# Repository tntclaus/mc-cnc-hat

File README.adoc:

= Makers' Comrade CNC HAT

Модели шилдов, которые превращают Raspberry в много-осевой ЧПУ с высокой производительностью.

Поддерживаются Raspberry Pi 3B, 3B+, 4 и другие микрокомпьютеры семейства Pi, с колодкой имеющей 40 gpio  (например, Orange Pi 3B).

== Модели

// === 5-осевой шилд
//
// //TODO:
//
// С независимыми UART линиями, в первую очередь для TMC2208, TMC2209 или для DRV8820, A4988 — обычный режим с конфигурацией через перемычки MS1,MS2,MS3 и других драйвера, поддерживающие DIR/STEP.
//
// xref:kicad/mc_cnc_hat_x5/README.adoc[]
//

=== 7-осевой шилд с CAN bus

image::docs/photo_mc_cnc_hat_x7_canbus.jpeg[]

Шилд для управления 7 двигателями ЧПУ и CAN bus периферией для Raspberry Pi 3B/3B+/4B и Orange Pi 3B (не проверялось, но должно работать).

xref:kicad/mc_cnc_hat_x7_canbus/README.adoc[]

=== 8-осевой шилд

image::docs/photo_mc_cnc_hat_x8.png[]

С двумя общими UART линиями для драйверов TMC2209 или для DRV8820, A4988 — обычный режим с конфигурацией через перемычки MS1,MS2,MS3 и других драйвера, поддерживающие DIR/STEP.

xref:kicad/mc_cnc_hat_x7_canbus/README.adoc[]

== Общие для всех моделей возможности

* Одновременное управление 5-7 драйверами шаговых двигателей:
** Поддерживаемые драйвера:
*** TMC2209, TMC2208 — режим UART с указанием адреса через перемычки MS1/MS2;
*** DRV8820, A4988 — обычный режим с конфигурацией через перемычки MS1,MS2,MS3;
*** Любые другие драйвера, поддерживающие DIR/STEP.
* Суммарная пиковая производительность всех двигателей 1018 тыс. шагов/секунду (Klipper с патчем, Linux CNC не тестировался, но вероятно будет результат того же порядка).
* Поддержка концевиков для осей X, Y, Z, A, B, C как стандартного типа, так и DIAG выходов для безсенсорной парковки драйвера TMC2209.
* Поддержка дополнительного концевика (например, для датчика наличия/движения филамента 3д принтера).
* Поддерживаемые системы: Linux CNC (не тестировалось), Klipper.

== Инструкция по установке

Инструкция тут: xref:docs/klipper.adoc[]

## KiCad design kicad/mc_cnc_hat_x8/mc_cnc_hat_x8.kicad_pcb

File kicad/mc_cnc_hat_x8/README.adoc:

= Makers' Comrade CNC Hat (x8 drivers)

image::../../docs/photo_mc_cnc_hat_x8.png[]

Шилд для управления 8 двигателями ЧПУ для Raspberry Pi 3B/3B+/4B и Orange Pi 3B (не проверялось, но должно работать).

С двумя общими UART линиями для драйверов TMC2209 или для DRV8820, A4988 — обычный режим с конфигурацией через перемычки MS1,MS2,MS3 и других драйвера, поддерживающие DIR/STEP.

TMC2208 можно установить по 1 на каждую UART линию, при условии что на остальных местах будут драйвера не требующие использования UART (например, DRV8820).

Первая UART линия общая для X, X1, Y, Z.
Вторая UART линия общая для A, A1, B, C.

== Возможности

* Одновременное управление 8 драйверами шаговых двигателей. Поддерживаемые драйвера:
** TMC2209 — режим UART с указанием адреса через перемычки MS1/MS2;
** TMC2208, DRV8820, A4988 — обычный режим с конфигурацией через перемычки MS1,MS2,MS3;
** Любые другие драйвера, поддерживающие DIR/STEP.
* Суммарная пиковая производительность всех двигателей 1018 тыс. шагов/секунду на RPi 3B+ (Klipper из форка https://github.com/tntclaus/klipper[tntclaus/klipper], Linux CNC не тестировался, но вероятно будет результат того же порядка).
* Поддержка концевиков для всех двигателей — как стандартного типа, так и DIAG выходов для безсенсорной парковки драйвера TMC2209.
* Поддерживаемые системы: Linux CNC (не тестировалось), Klipper.

== Использование

Для использования с Klipper см. инструкцию xref:../../docs/klipper.adoc[по настройке Klipper]

Конфигурирование драйверов описано в  xref:../../docs/drivers_x7_x8.adoc[инструкции].

== Пины

.Моторы
|===
|Назначение |Motor X |Motor X1 |Motor Y |Motor Z |Motor A |Motor A1 |Motor B |Motor C

|STEP
|GPIO3
|GPIO6
|GPIO27
|GPIO19
|GPIO23
|GPIO9
|GPIO1
|GPIO20

|DIR
|GPIO2
|GPIO15
|GPIO17
|GPIO13
|GPIO24
|GPIO10
|GPIO12
|GPIO21

|UART
|GPIO5
|GPIO5
|GPIO5
|GPIO5
|GPIO25
|GPIO25
|GPIO25
|GPIO25

|DIAG/Endstop
|GPIO4
|GPIO11
|GPIO0
|GPIO26
|GPIO18
|GPIO8
|GPIO7
|GPIO16
|===

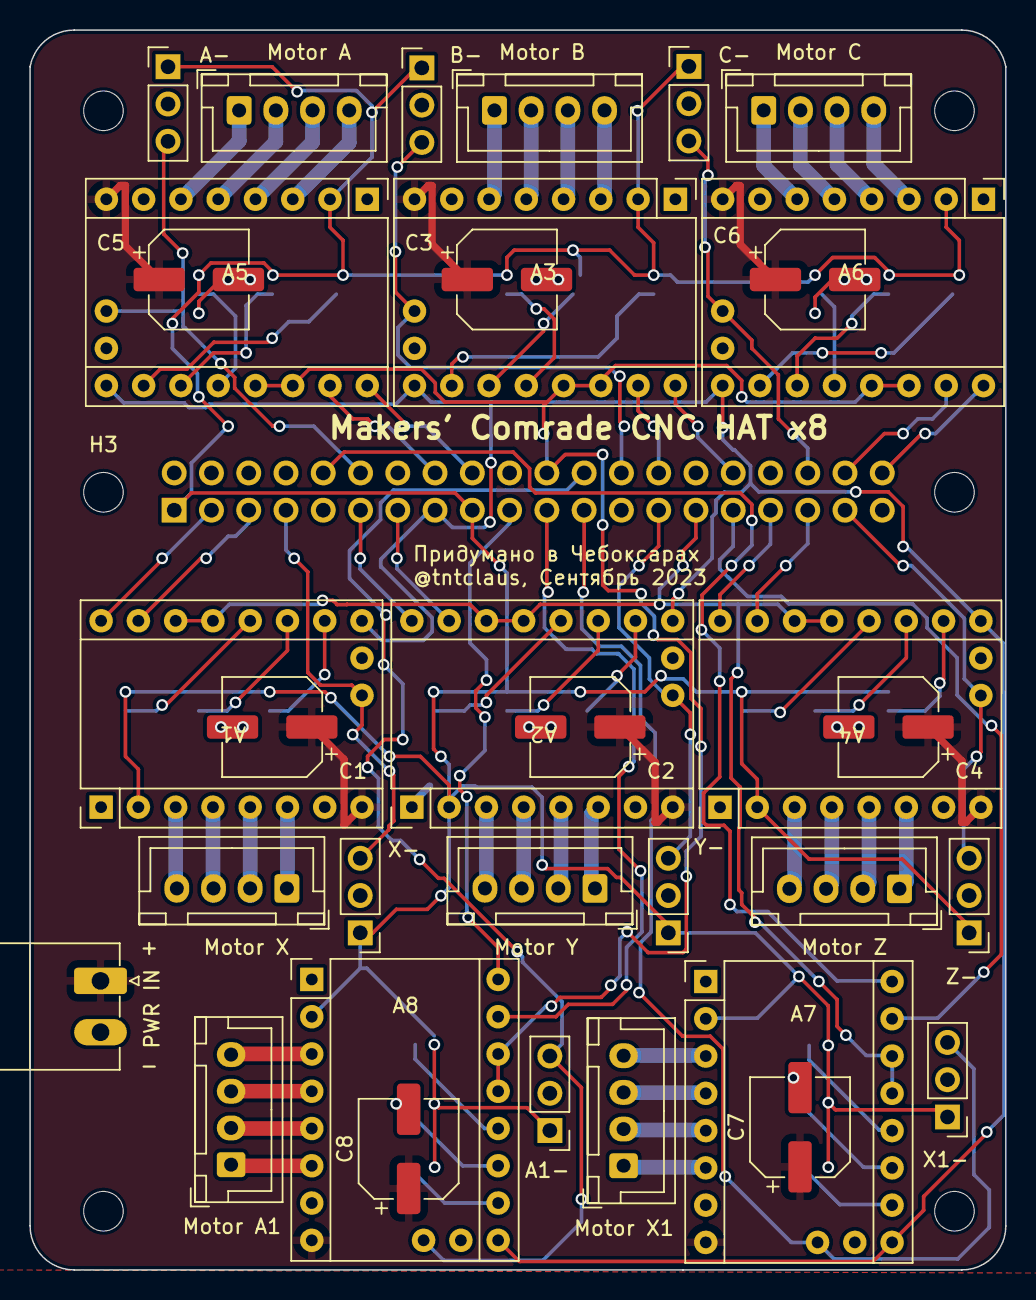
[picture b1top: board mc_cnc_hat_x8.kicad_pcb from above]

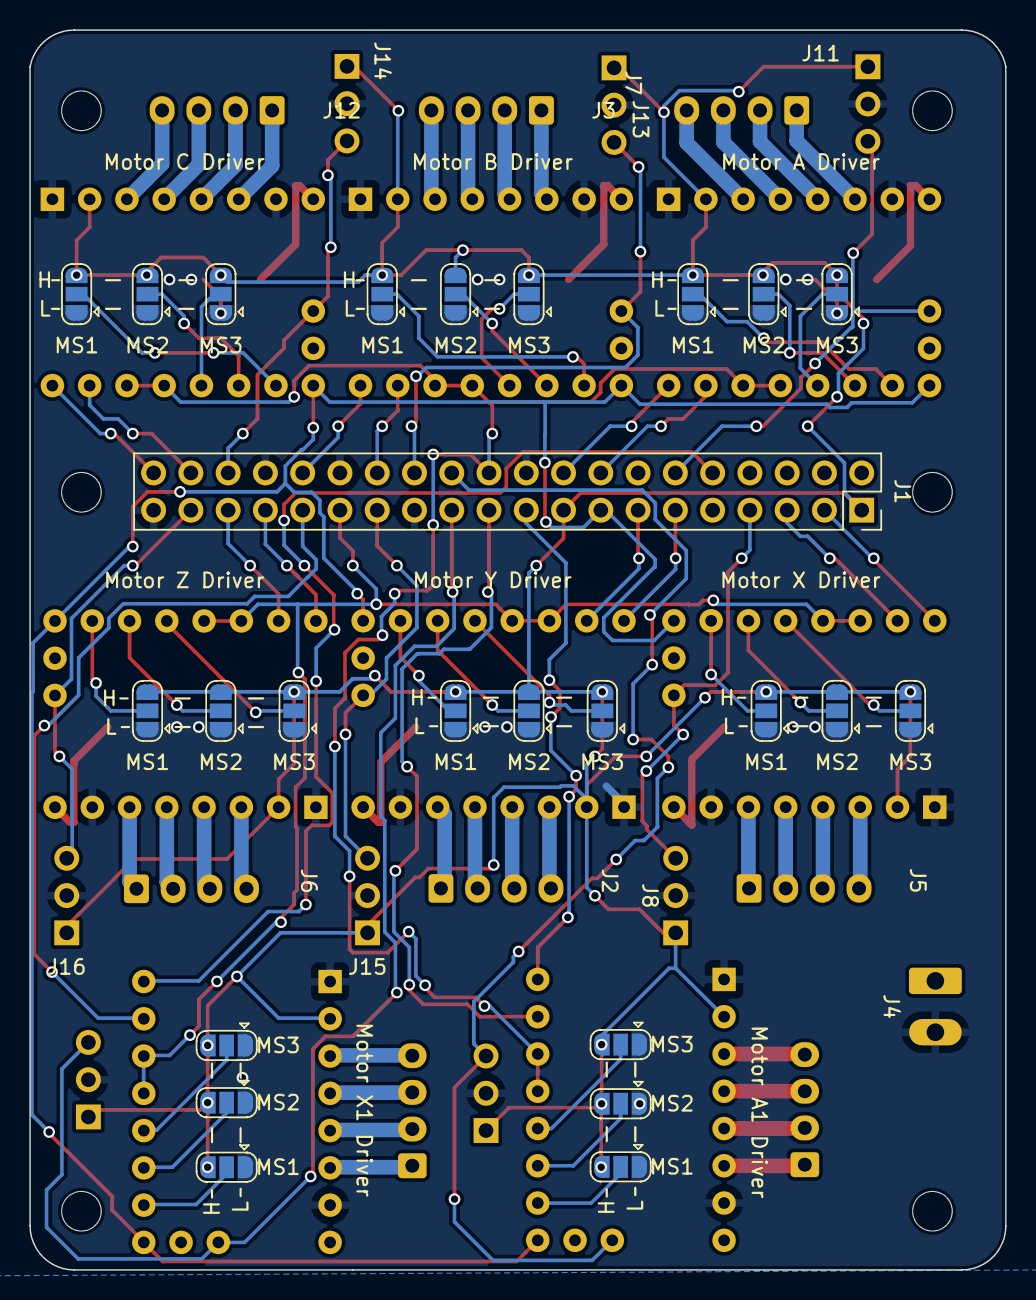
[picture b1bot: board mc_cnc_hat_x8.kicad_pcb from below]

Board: 2 copper layers, 66.5 x 84.5 mm, 64 parts (25 on the bottom side), 86 nets.

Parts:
A1: Motor X Driver; TMC220X
A2: Motor Y Driver; TMC220X
A3: Motor B Driver; TMC220X
A4: Motor Z Driver; TMC220X
A5: Motor A Driver; TMC220X
A6: Motor C Driver; TMC220X
A7: Motor X1 Driver; TMC220X
A8: Motor A1 Driver; TMC220X
C1, C2, C3, C4, C5, C6, C7, C8: 100µF 50V; CP_Elec_6.3x7.7
H1, H2, H3, H4, H5, H6: MountingHole; MountingHole_2.7mm_M2.5_ISO14580
J1: Raspberry_Pi_2_3; PinSocket_2x20_P2.54mm_Vertical
J2: Motor Y; JST_XH_B4B-XH-A_1x04_P2.50mm_Vertical
J3: Motor B; JST_XH_B4B-XH-A_1x04_P2.50mm_Vertical
J4: PWR IN; PhoenixContact_MC_1,5_2-G-3.5_1x02_P3.50mm_Horizontal
J5: Motor X; JST_XH_B4B-XH-A_1x04_P2.50mm_Vertical
J6: Motor Z; JST_XH_B4B-XH-A_1x04_P2.50mm_Vertical
J7: Motor A; JST_XH_B4B-XH-A_1x04_P2.50mm_Vertical
J8: X-; PinHeader_1x03_P2.54mm_Vertical
J9: X1-; PinHeader_1x03_P2.54mm_Vertical
J10: A1-; PinHeader_1x03_P2.54mm_Vertical
J11: A-; PinHeader_1x03_P2.54mm_Vertical
J12: Motor C; JST_XH_B4B-XH-A_1x04_P2.50mm_Vertical
J13: B-; PinHeader_1x03_P2.54mm_Vertical
J14: C-; PinHeader_1x03_P2.54mm_Vertical
J15: Y-; PinHeader_1x03_P2.54mm_Vertical
J16: Z-; PinHeader_1x03_P2.54mm_Vertical
J17: Motor X1; JST_XH_B4B-XH-A_1x04_P2.50mm_Vertical
J18: Motor A1; JST_XH_B4B-XH-A_1x04_P2.50mm_Vertical
JP1, JP4, JP7, JP10, JP13, JP16, JP19, JP22: MS3; SolderJumper-3_P1.3mm_Open_RoundedPad1.0x1.5mm
JP2, JP5, JP8, JP11, JP14, JP17, JP20, JP23: MS2; SolderJumper-3_P1.3mm_Open_RoundedPad1.0x1.5mm
JP3, JP6, JP9, JP12, JP15, JP18, JP21, JP24: MS1; SolderJumper-3_P1.3mm_Open_RoundedPad1.0x1.5mm

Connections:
+3V3: A1.2 (VDD), A2.2 (VDD), A3.2 (VDD), A4.2 (VDD), A5.2 (VDD), A6.2 (VDD), A7.2 (VDD), A8.2 (VDD), J1.1 (3V3), J1.17 (3V3), J8.1, J9.1, J10.1, J11.1, J13.1, J14.1, J15.1, J16.1, JP1.3 (B), JP2.3 (B), JP3.3 (B), JP4.3 (B), JP5.3 (B), JP6.3 (B), JP7.3 (B), JP8.3 (B), JP9.3 (B), JP10.3 (B), JP11.3 (B), JP12.3 (B), JP13.3 (B), JP14.3 (B), JP15.3 (B), JP16.3 (B), JP17.3 (B), JP18.3 (B), JP19.3 (B), JP20.3 (B), JP21.3 (B), JP22.3 (B), JP23.3 (B), JP24.3 (B)
/MA1 DIAG: A8.18 (DIAG), J1.24 (~CE0/GPIO8), J10.3
/MA1 DIR: A8.16 (DIR), J1.19 (MOSI0/GPIO10)
/MA1 STEP: A8.15 (STEP), J1.21 (MISO0/GPIO9)
/MA DIAG: A5.18 (DIAG), J1.12 (GPIO18/PWM0), J11.3
/MA DIR: A5.16 (DIR), J1.18 (GPIO24)
/MA STEP: A5.15 (STEP), J1.16 (GPIO23)
/MB DIAG: A3.18 (DIAG), J1.26 (~CE1/GPIO7), J13.3
/MB DIR: A3.16 (DIR), J1.32 (PWM0/GPIO12)
/MB STEP: A3.15 (STEP), J1.28 (ID_SC/GPIO1)
/MC DIAG: A6.18 (DIAG), J1.36 (GPIO16), J14.3
/MC DIR: A6.16 (DIR), J1.40 (GPIO21/SCLK1)
/MC STEP: A6.15 (STEP), J1.38 (GPIO20/MOSI1)
/MX1 DIAG: A7.18 (DIAG), J1.23 (SCLK0/GPIO11), J9.3
/MX1 DIR: A7.16 (DIR), J1.10 (GPIO15/RXD)
/MX1 STEP: A7.15 (STEP), J1.31 (GCLK2/GPIO6)
/MX DIAG: A1.18 (DIAG), J1.7 (GCLK0/GPIO4), J8.3
/MX DIR: A1.16 (DIR), J1.3 (SDA/GPIO2)
/MX STEP: A1.15 (STEP), J1.5 (SCL/GPIO3)
/MY DIAG: A2.18 (DIAG), J1.27 (ID_SD/GPIO0), J15.3
/MY DIR: A2.16 (DIR), J1.11 (GPIO17)
/MY STEP: A2.15 (STEP), J1.13 (GPIO27)
/MZ DIAG: A4.18 (DIAG), J1.37 (GPIO26), J16.3
/MZ DIR: A4.16 (DIR), J1.33 (PWM1/GPIO13)
/MZ STEP: A4.15 (STEP), J1.35 (GPIO19/MISO1)
/Motor A1/1A: A8.4 (1A), J18.3
/Motor A1/1B: A8.3 (1B), J18.4
/Motor A1/2A: A8.5 (2A), J18.2
/Motor A1/2B: A8.6 (2B), J18.1
/Motor A1/MS1: A8.10 (MS1), JP24.2 (C)
/Motor A1/MS2: A8.11 (MS2), JP23.2 (C)
/Motor A1/MS3: A8.12 (NC/TX), JP22.2 (C)
/Motor A/1A: A5.4 (1A), J7.3
/Motor A/1B: A5.3 (1B), J7.4
/Motor A/2A: A5.5 (2A), J7.2
/Motor A/2B: A5.6 (2B), J7.1
/Motor A/MS1: A5.10 (MS1), JP15.2 (C)
/Motor A/MS2: A5.11 (MS2), JP14.2 (C)
/Motor A/MS3: A5.12 (NC/TX), JP13.2 (C)
/Motor B/1A: A3.4 (1A), J3.3
/Motor B/1B: A3.3 (1B), J3.4
/Motor B/2A: A3.5 (2A), J3.2
/Motor B/2B: A3.6 (2B), J3.1
/Motor B/MS1: A3.10 (MS1), JP9.2 (C)
/Motor B/MS2: A3.11 (MS2), JP8.2 (C)
/Motor B/MS3: A3.12 (NC/TX), JP7.2 (C)
/Motor C/1A: A6.4 (1A), J12.3
/Motor C/1B: A6.3 (1B), J12.4
/Motor C/2A: A6.5 (2A), J12.2
/Motor C/2B: A6.6 (2B), J12.1
/Motor C/MS1: A6.10 (MS1), JP18.2 (C)
/Motor C/MS2: A6.11 (MS2), JP17.2 (C)
/Motor C/MS3: A6.12 (NC/TX), JP16.2 (C)
/Motor X1/1A: A7.4 (1A), J17.3
/Motor X1/1B: A7.3 (1B), J17.4
/Motor X1/2A: A7.5 (2A), J17.2
/Motor X1/2B: A7.6 (2B), J17.1
/Motor X1/MS1: A7.10 (MS1), JP21.2 (C)
/Motor X1/MS2: A7.11 (MS2), JP20.2 (C)
/Motor X1/MS3: A7.12 (NC/TX), JP19.2 (C)
/Motor X/1A: A1.4 (1A), J5.3
/Motor X/1B: A1.3 (1B), J5.4
/Motor X/2A: A1.5 (2A), J5.2
/Motor X/2B: A1.6 (2B), J5.1
/Motor X/MS1: A1.10 (MS1), JP3.2 (C)
/Motor X/MS2: A1.11 (MS2), JP2.2 (C)
/Motor X/MS3: A1.12 (NC/TX), JP1.2 (C)
/Motor Y/1A: A2.4 (1A), J2.3
/Motor Y/1B: A2.3 (1B), J2.4
/Motor Y/2A: A2.5 (2A), J2.2
/Motor Y/2B: A2.6 (2B), J2.1
/Motor Y/MS1: A2.10 (MS1), JP6.2 (C)
/Motor Y/MS2: A2.11 (MS2), JP5.2 (C)
/Motor Y/MS3: A2.12 (NC/TX), JP4.2 (C)
/Motor Z/1A: A4.4 (1A), J6.3
/Motor Z/1B: A4.3 (1B), J6.4
/Motor Z/2A: A4.5 (2A), J6.2
/Motor Z/2B: A4.6 (2B), J6.1
/Motor Z/MS1: A4.10 (MS1), JP12.2 (C)
/Motor Z/MS2: A4.11 (MS2), JP11.2 (C)
/Motor Z/MS3: A4.12 (NC/TX), JP10.2 (C)
/UART_A: A3.13 (PDN/RX), A3.14 (NC/CLK), A5.13 (PDN/RX), A5.14 (NC/CLK), A6.13 (PDN/RX), A6.14 (NC/CLK), A8.13 (PDN/RX), A8.14 (NC/CLK), J1.22 (GPIO25)
/UART_X: A1.13 (PDN/RX), A1.14 (NC/CLK), A2.13 (PDN/RX), A2.14 (NC/CLK), A4.13 (PDN/RX), A4.14 (NC/CLK), A7.13 (PDN/RX), A7.14 (NC/CLK), J1.29 (GCLK1/GPIO5)
GND: A1.1 (GND), A1.7 (GND), A2.1 (GND), A2.7 (GND), A3.1 (GND), A3.7 (GND), A4.1 (GND), A4.7 (GND), A5.1 (GND), A5.7 (GND), A6.1 (GND), A6.7 (GND), A7.1 (GND), A7.7 (GND), A8.1 (GND), A8.7 (GND), C1.2, C2.2, C3.2, C4.2, C5.2, C6.2, C7.2, C8.2, J1.20 (GND), J1.25 (GND), J1.30 (GND), J1.34 (GND), J1.39 (GND), J4.2, J8.2, J9.2, J10.2, J11.2, J13.2, J14.2, J15.2, J16.2, JP1.1 (A), JP2.1 (A), JP3.1 (A), JP4.1 (A), JP5.1 (A), JP6.1 (A), JP7.1 (A), JP8.1 (A), JP9.1 (A), JP10.1 (A), JP11.1 (A), JP12.1 (A), JP13.1 (A), JP14.1 (A), JP15.1 (A), JP16.1 (A), JP17.1 (A), JP18.1 (A), JP19.1 (A), JP20.1 (A), JP21.1 (A), JP22.1 (A), JP23.1 (A), JP24.1 (A)
MEN: A1.9 (~ENABLE), A2.9 (~ENABLE), A3.9 (~ENABLE), A4.9 (~ENABLE), A5.9 (~ENABLE), A6.9 (~ENABLE), A7.9 (~ENABLE), A8.9 (~ENABLE), J1.15 (GPIO22)
Vin: A1.8 (VMOT), A2.8 (VMOT), A3.8 (VMOT), A4.8 (VMOT), A5.8 (VMOT), A6.8 (VMOT), A7.8 (VMOT), A8.8 (VMOT), C1.1, C2.1, C3.1, C4.1, C5.1, C6.1, C7.1, C8.1, J4.1

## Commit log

2023-09-12 initial commit with x7 can bus capable model
2023-09-12 GPIO pin map
2023-09-12 руководство по конфигурированию драйверов
2023-09-12 fix main illustration
2023-09-12 добавлена версия с 8 драйверами
